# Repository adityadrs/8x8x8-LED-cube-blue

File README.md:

8x8x8 LED Cube Blue

Sources contain original files (design and code) that I used to build my cube around

Code added to impliment multiplexing, there are some issues with dynamic implimentation but when things are hard coded, multiplexing works fine ( Basic.ino )

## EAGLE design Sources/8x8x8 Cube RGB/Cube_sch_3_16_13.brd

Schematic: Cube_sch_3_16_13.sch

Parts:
C1, C6, C7, C16, C17, C18, C19, C20, C21, C22, C23, C24, C25, C26, C27, C28, C29, C30, C31, C32, C33, C34, C35, C36, C37, C38: 0.1uF; C2.5-3
C2: 10uF; C2.5-3
C3, C8, C9, C10, C11, C12, C13, C14, C15: 100uF; C2.5-3
C4, C5: 22pf; C2.5-3
C39: 0.1uf; C2.5-3
IC1, IC3, IC4, IC5, IC6, IC7, IC8, IC9, IC10, IC11, IC12, IC13, IC14, IC15, IC16, IC17, IC18, IC19, IC20, IC21, IC22, IC23, IC24, IC25, IC26: 74HC595N; DIL16
IC2: SMARTPRJ_ATMEGA328P-PU; SMARTPRJ_DIL28-3
Q1: 16MHz; HC49/S
Q2, Q3, Q4, Q5, Q6, Q7, Q8, Q9: IRF9Z34N; TO220BV
R1, R3, R5, R6, R8, R9, R11, R12, R14, R15, R17, R18, R20, R21, R23, R24, R26, R27, R30, R31, R34, R35, R38, R39, R42, R43, R46, R47, R50, R51, R54, R55, R58, R59, R62, R63, R66, R67, R70, R71, R74, R75, R78, R79, R82, R83, R86, R87, R90, R91, R94, R95, R98, R99, R102, R103, R106, R107, R110, R111, R114, R115, R118, R119, R122, R123, R126, R127, R130, R131, R134, R135, R138, R139, R142, R143, R146, R147, R150, R151, R154, R155, R158, R159, R162, R163, R166, R167, R170, R171, R174, R175, R178, R179, R182, R183, R186, R187, R190, R191, R194, R195, R198, R199, R202, R203, R206, R207, R210, R211, R214, R215, R218, R219, R222, R223, R226, R227, R230, R231, R234, R235, R238, R239, R242, R243, R246, R247, R250, R251, R254, R255, R258, R259, R262, R263, R266, R267, R270, R271, R274, R275, R278, R279, R282, R283, R286, R287, R290, R291, R294, R295, R298, R299, R302, R303, R306, R307, R310, R311, R314, R315, R318, R319, R322, R323, R326, R327, R330, R331, R334, R335, R338, R339, R342, R343, R346, R347, R350, R351, R354, R355, R358, R359, R362, R363, R366, R367, R370, R371, R374, R375, R378, R379, R382, R383, R386, R387, R390, R391, R394, R395, R398, R399, R402, R403, R406, R407, R410, R411, R414, R415, R418, R419, R422, R423, R426, R427, R430, R431, R434, R435, R438, R439, R442, R443, R446, R447, R450, R451, R454, R455, R458, R459, R462, R463, R466, R467, R470, R471, R474, R475, R478, R479, R482, R483, R486, R487, R490, R491, R494, R495, R498, R499, R502, R503, R506, R507, R510, R511, R514, R515, R518, R519, R522, R523, R526, R527, R530, R531, R534, R535, R538, R539, R541, R542, R543, R545, R546, R547, R550, R551, R553, R554, R555, R557, R558, R559, R562, R563, R565, R566, R567, R569, R571, R572, R574, R575, R577, R578, R580, R581, R583, R584, R586, R587, R589, R590, R592, R593, R595, R596, R598, R599, R601, R602, R604, R605, R607, R608, R610, R611, R613, R614, R616, R617, R619, R620, R622, R623, R625, R626, R628, R629, R631, R632, R634, R635, R637, R638, R640, R641, R643, R644, R646, R647, R649, R650, R652, R653, R655, R656, R658, R659, R661, R662, R664, R665, R667, R668, R670, R671, R673, R674, R676, R677, R679, R680, R682, R683, R685, R686, R688, R689, R691, R692, R694, R695, R697, R698, R700, R701, R703, R704, R706, R707, R709, R710, R712, R713, R715, R716, R718, R719, R721, R722, R724, R725, R727, R728: 1k; 0204/5
R2, R730: 10k; 0204/5
R4, R7, R10, R13, R16, R19, R22, R25, R28, R29, R32, R33, R36, R37, R40, R41, R44, R45, R48, R49, R52, R53, R56, R57, R60, R61, R64, R65, R68, R69, R72, R73, R76, R77, R80, R81, R84, R85, R88, R89, R92, R93, R96, R97, R100, R101, R104, R105, R108, R109, R112, R113, R116, R117, R120, R121, R124, R125, R128, R129, R132, R133, R136, R137, R140, R141, R144, R145, R148, R149, R152, R153, R156, R157, R160, R161, R164, R165, R168, R169, R172, R173, R176, R177, R180, R181, R184, R185, R188, R189, R192, R193, R196, R197, R200, R201, R204, R205, R208, R209, R212, R213, R216, R217, R220, R221, R224, R225, R228, R229, R232, R233, R236, R237, R240, R241, R244, R245, R248, R249, R252, R253, R256, R257, R260, R261, R264, R265, R268, R269, R272, R273, R276, R277, R280, R281, R284, R285, R288, R289, R292, R293, R296, R297, R300, R301, R304, R305, R308, R309, R312, R313, R316, R317, R320, R321, R324, R325, R328, R329, R332, R333, R336, R337, R340, R341, R344, R345, R348, R349, R352, R353, R356, R357, R360, R361, R364, R365, R368, R369, R372, R373, R376, R377, R380, R381, R384, R385, R388, R389, R392, R393, R396, R397, R400, R401, R404, R405, R408, R409, R412, R413, R416, R417, R420, R421, R424, R425, R428, R429, R432, R433, R436, R437, R440, R441, R444, R445, R448, R449, R452, R453, R456, R457, R460, R461, R464, R465, R468, R469, R472, R473, R476, R477, R480, R481, R484, R485, R488, R489, R492, R493, R496, R497, R500, R501, R504, R505, R508, R509, R512, R513, R516, R517, R520, R521, R524, R525, R528, R529, R532, R533, R536, R537, R540, R544, R548, R549, R552, R556, R560, R561, R564, R568, R570, R573, R576, R579, R582, R585, R588, R591, R594, R597, R600, R603, R606, R609, R612, R615, R618, R621, R624, R627, R630, R633, R636, R639, R642, R645, R648, R651, R654, R657, R660, R663, R666, R669, R672, R675, R678, R681, R684, R687, R690, R693, R696, R699, R702, R705, R708, R711, R714, R717, R720, R723, R726, R729: 100; 0204/5
SV1: MA04-1
SV2: MA05-1
T1, T2, T3, T4, T5, T6, T7, T8, T9, T10, T11, T12, T13, T14, T15, T16, T17, T18, T19, T20, T21, T22, T23, T24, T25, T26, T27, T28, T29, T30, T31, T32, T33, T34, T35, T36, T37, T38, T39, T40, T41, T42, T43, T44, T45, T46, T47, T48, T49, T50, T51, T52, T53, T54, T55, T56, T57, T58, T59, T60, T61, T62, T63, T64, T65, T66, T67, T68, T69, T70, T71, T72, T73, T74, T75, T76, T77, T78, T79, T80, T81, T82, T83, T84, T85, T86, T87, T88, T89, T90, T91, T92, T93, T94, T95, T96, T97, T98, T99, T100, T101, T102, T103, T104, T105, T106, T107, T108, T109, T110, T111, T112, T113, T114, T115, T116, T117, T118, T119, T120, T121, T122, T123, T124, T125, T126, T127, T128, T129, T130, T131, T132, T133, T134, T135, T136, T137, T138, T139, T140, T141, T142, T143, T144, T145, T146, T147, T148, T149, T150, T151, T152, T153, T154, T155, T156, T157, T158, T159, T160, T161, T162, T163, T164, T165, T166, T167, T168, T169, T170, T171, T172, T173, T174, T175, T176, T177, T178, T179, T180, T181, T182, T183, T184, T185, T186, T187, T188, T189, T190, T191, T192, T193, T194, T195, T196, T197, T198, T199, T200: 2N3904; TO92

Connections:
+5V: C1.1, C2.1, C3.1, C6.1, C7.1, C8.1, C9.1, C10.1, C11.1, C12.1, C13.1, C14.1, C15.1, C16.1, C17.1, C18.1, C19.1, C20.1, C21.1, C22.1, C23.1, C24.1, C25.1, C26.1, C27.1, C28.1, C29.1, C30.1, C31.1, C32.1, C33.1, C34.1, C35.1, C36.1, C37.1, C38.1, IC1.10 (SCL), IC1.16 (VCC), IC2.7 (VCC), IC2.20 (AVCC), IC2.21 (AREF), IC3.10 (SCL), IC3.16 (VCC), IC4.10 (SCL), IC4.16 (VCC), IC5.10 (SCL), IC5.16 (VCC), IC6.10 (SCL), IC6.16 (VCC), IC7.10 (SCL), IC7.16 (VCC), IC8.10 (SCL), IC8.16 (VCC), IC9.10 (SCL), IC9.16 (VCC), IC10.10 (SCL), IC10.16 (VCC), IC11.10 (SCL), IC11.16 (VCC), IC12.10 (SCL), IC12.16 (VCC), IC13.10 (SCL), IC13.16 (VCC), IC14.10 (SCL), IC14.16 (VCC), IC15.10 (SCL), IC15.16 (VCC), IC16.10 (SCL), IC16.16 (VCC), IC17.10 (SCL), IC17.16 (VCC), IC18.10 (SCL), IC18.16 (VCC), IC19.10 (SCL), IC19.16 (VCC), IC20.10 (SCL), IC20.16 (VCC), IC21.10 (SCL), IC21.16 (VCC), IC22.10 (SCL), IC22.16 (VCC), IC23.10 (SCL), IC23.16 (VCC), IC24.10 (SCL), IC24.16 (VCC), IC25.10 (SCL), IC25.16 (VCC), IC26.10 (SCL), IC26.16 (VCC), Q2.S, Q3.S, Q4.S, Q5.S, Q6.S, Q7.S, Q8.S, Q9.S, R2.2, R3.2, R6.2, R9.2, R12.2, R15.2, R18.2, R21.2, R24.2, R27.2, R31.2, R35.2, R39.2, R43.2, R47.2, R51.2, R55.2, R59.2, R63.2, R67.2, R71.2, R75.2, R79.2, R83.2, R87.2, R91.2, R95.2, R99.2, R103.2, R107.2, R111.2, R115.2, R119.2, R123.2, R127.2, R131.2, R135.2, R139.2, R143.2, R147.2, R151.2, R155.2, R159.2, R163.2, R167.2, R171.2, R175.2, R179.2, R183.2, R187.2, R191.2, R195.2, R199.2, R203.2, R207.2, R211.2, R215.2, R219.2, R223.2, R227.2, R231.2, R235.2, R239.2, R243.2, R247.2, R251.2, R255.2, R259.2, R263.2, R267.2, R271.2, R275.2, R279.2, R283.2, R287.2, R291.2, R295.2, R299.2, R303.2, R307.2, R311.2, R315.2, R319.2, R323.2, R327.2, R331.2, R335.2, R339.2, R343.2, R347.2, R351.2, R355.2, R359.2, R363.2, R367.2, R371.2, R375.2, R379.2, R383.2, R387.2, R391.2, R395.2, R399.2, R403.2, R407.2, R411.2, R415.2, R419.2, R423.2, R427.2, R431.2, R435.2, R439.2, R443.2, R447.2, R451.2, R455.2, R459.2, R463.2, R467.2, R471.2, R475.2, R479.2, R483.2, R487.2, R491.2, R495.2, R499.2, R503.2, R507.2, R511.2, R515.2, R519.2, R523.2, R527.2, R531.2, R535.2, R539.2, R543.2, R545.2, R547.2, R551.2, R555.2, R557.2, R559.2, R563.2, R567.2, R569.2, R572.2, R575.2, R578.2, R581.2, R584.2, R587.2, R590.2, R593.2, R596.2, R599.2, R602.2, R605.2, R608.2, R611.2, R614.2, R617.2, R620.2, R623.2, R626.2, R629.2, R632.2, R635.2, R638.2, R641.2, R644.2, R647.2, R650.2, R653.2, R656.2, R659.2, R662.2, R665.2, R668.2, R671.2, R674.2, R677.2, R680.2, R683.2, R686.2, R689.2, R692.2, R695.2, R698.2, R701.2, R704.2, R707.2, R710.2, R713.2, R716.2, R719.2, R722.2, R725.2, R728.2, SV1.2
ANODE_LEVEL_0: Q2.D, R4.2
ANODE_LEVEL_1: Q3.D, R7.2
ANODE_LEVEL_2: Q4.D, R10.2
ANODE_LEVEL_3: Q5.D, R13.2
ANODE_LEVEL_4: Q6.D, R16.2
ANODE_LEVEL_5: Q7.D, R19.2
ANODE_LEVEL_6: Q8.D, R22.2
ANODE_LEVEL_7: Q9.D, R25.2
BLANK: IC1.13 (G), IC2.6 ((T0)PD4), IC3.13 (G), IC4.13 (G), IC5.13 (G), IC6.13 (G), IC7.13 (G), IC8.13 (G), IC9.13 (G), IC10.13 (G), IC11.13 (G), IC12.13 (G), IC13.13 (G), IC14.13 (G), IC15.13 (G), IC16.13 (G), IC17.13 (G), IC18.13 (G), IC19.13 (G), IC20.13 (G), IC21.13 (G), IC22.13 (G), IC23.13 (G), IC24.13 (G), IC25.13 (G), IC26.13 (G), R2.1
BL_IN_0: IC1.15 (QA), R26.1
BL_IN_1: IC1.1 (QB), R30.1
BL_IN_2: IC1.2 (QC), R34.1
BL_IN_3: IC1.3 (QD), R38.1
BL_IN_4: IC1.4 (QE), R42.1
BL_IN_5: IC1.5 (QF), R46.1
BL_IN_6: IC1.6 (QG), R50.1
BL_IN_7: IC1.7 (QH), R54.1
BL_IN_8: IC4.15 (QA), R58.1
BL_IN_9: IC4.1 (QB), R62.1
BL_IN_10: IC4.2 (QC), R66.1
BL_IN_11: IC4.3 (QD), R70.1
BL_IN_12: IC4.4 (QE), R74.1
BL_IN_13: IC4.5 (QF), R78.1
BL_IN_14: IC4.6 (QG), R82.1
BL_IN_15: IC4.7 (QH), R86.1
BL_IN_16: IC5.15 (QA), R90.1
BL_IN_17: IC5.1 (QB), R94.1
BL_IN_18: IC5.2 (QC), R98.1
BL_IN_19: IC5.3 (QD), R102.1
BL_IN_20: IC5.4 (QE), R106.1
BL_IN_21: IC5.5 (QF), R110.1
BL_IN_22: IC5.6 (QG), R114.1
BL_IN_23: IC5.7 (QH), R118.1
BL_IN_24: IC6.15 (QA), R122.1
BL_IN_25: IC6.1 (QB), R126.1
BL_IN_26: IC6.2 (QC), R130.1
BL_IN_27: IC6.3 (QD), R134.1
BL_IN_28: IC6.4 (QE), R138.1
BL_IN_29: IC6.5 (QF), R142.1
BL_IN_30: IC6.6 (QG), R146.1
BL_IN_31: IC6.7 (QH), R150.1
BL_IN_32: IC7.15 (QA), R154.1
BL_IN_33: IC7.1 (QB), R158.1
BL_IN_34: IC7.2 (QC), R162.1
BL_IN_35: IC7.3 (QD), R166.1
BL_IN_36: IC7.4 (QE), R170.1
BL_IN_37: IC7.5 (QF), R174.1
BL_IN_38: IC7.6 (QG), R178.1
BL_IN_39: IC7.7 (QH), R182.1
BL_IN_40: IC8.15 (QA), R186.1
BL_IN_41: IC8.1 (QB), R190.1
BL_IN_42: IC8.2 (QC), R194.1
BL_IN_43: IC8.3 (QD), R198.1
BL_IN_44: IC8.4 (QE), R202.1
BL_IN_45: IC8.5 (QF), R206.1
BL_IN_46: IC8.6 (QG), R210.1
BL_IN_47: IC8.7 (QH), R214.1
BL_IN_48: IC9.15 (QA), R218.1
BL_IN_49: IC9.1 (QB), R222.1
BL_IN_50: IC9.2 (QC), R226.1
BL_IN_51: IC9.3 (QD), R230.1
BL_IN_52: IC9.4 (QE), R234.1
BL_IN_53: IC9.5 (QF), R238.1
BL_IN_54: IC9.6 (QG), R242.1
BL_IN_55: IC9.7 (QH), R246.1
BL_IN_56: IC10.15 (QA), R250.1
BL_IN_57: IC10.1 (QB), R254.1
BL_IN_58: IC10.2 (QC), R258.1
BL_IN_59: IC10.3 (QD), R262.1
BL_IN_60: IC10.4 (QE), R266.1
BL_IN_61: IC10.5 (QF), R270.1
BL_IN_62: IC10.6 (QG), R274.1
BL_IN_63: IC10.7 (QH), R278.1
BL_OU_0: R28.2, R29.2
BL_OU_1: R32.2, R33.2
BL_OU_2: R36.2, R37.2
BL_OU_3: R40.2, R41.2
BL_OU_4: R44.2, R45.2
BL_OU_5: R48.2, R49.2
BL_OU_6: R52.2, R53.2
BL_OU_7: R56.2, R57.2
BL_OU_8: R60.2, R61.2
BL_OU_9: R64.2, R65.2
BL_OU_10: R68.2, R69.2
BL_OU_11: R72.2, R73.2
BL_OU_12: R76.2, R77.2
BL_OU_13: R80.2, R81.2
BL_OU_14: R84.2, R85.2
BL_OU_15: R88.2, R89.2
BL_OU_16: R92.2, R93.2
BL_OU_17: R96.2, R97.2
BL_OU_18: R100.2, R101.2
BL_OU_19: R104.2, R105.2
BL_OU_20: R108.2, R109.2
BL_OU_21: R112.2, R113.2
BL_OU_22: R116.2, R117.2
BL_OU_23: R120.2, R121.2
BL_OU_24: R124.2, R125.2
BL_OU_25: R128.2, R129.2
BL_OU_26: R132.2, R133.2
BL_OU_27: R136.2, R137.2
BL_OU_28: R140.2, R141.2
BL_OU_29: R144.2, R145.2
BL_OU_30: R148.2, R149.2
BL_OU_32: R152.2, R153.2, R156.2, R157.2
BL_OU_33: R160.2, R161.2
BL_OU_34: R164.2, R165.2
BL_OU_35: R168.2, R169.2
BL_OU_36: R172.2, R173.2
BL_OU_37: R176.2, R177.2
BL_OU_38: R180.2, R181.2
BL_OU_39: R184.2, R185.2
BL_OU_40: R188.2, R189.2
BL_OU_41: R192.2, R193.2
BL_OU_42: R196.2, R197.2
BL_OU_43: R200.2, R201.2
BL_OU_44: R204.2, R205.2
BL_OU_45: R208.2, R209.2
BL_OU_46: R212.2, R213.2
BL_OU_47: R216.2, R217.2
BL_OU_48: R220.2, R221.2
BL_OU_49: R224.2, R225.2
BL_OU_50: R228.2, R229.2
BL_OU_51: R232.2, R233.2
BL_OU_52: R236.2, R237.2
BL_OU_53: R240.2, R241.2
BL_OU_54: R244.2, R245.2
BL_OU_55: R248.2, R249.2
BL_OU_56: R252.2, R253.2
BL_OU_57: R256.2, R257.2
BL_OU_58: R260.2, R261.2
BL_OU_59: R264.2, R265.2
BL_OU_60: R268.2, R269.2
BL_OU_61: R272.2, R273.2
BL_OU_62: R276.2, R277.2
BL_OU_63: R280.2, R281.2
CLOCK: IC1.11 (SCK), IC2.19 ((SCK)PB5), IC3.11 (SCK), IC4.11 (SCK), IC5.11 (SCK), IC6.11 (SCK), IC7.11 (SCK), IC8.11 (SCK), IC9.11 (SCK), IC10.11 (SCK), IC11.11 (SCK), IC12.11 (SCK), IC13.11 (SCK), IC14.11 (SCK), IC15.11 (SCK), IC16.11 (SCK), IC17.11 (SCK), IC18.11 (SCK), IC19.11 (SCK), IC20.11 (SCK), IC21.11 (SCK), IC22.11 (SCK), IC23.11 (SCK), IC24.11 (SCK), IC25.11 (SCK), IC26.11 (SCK)
CNTRL_L0: IC3.7 (QH), R1.1
CNTRL_L1: IC3.6 (QG), R5.1
CNTRL_L2: IC3.5 (QF), R8.1
CNTRL_L3: IC3.4 (QE), R11.1
CNTRL_L4: IC3.3 (QD), R14.1
CNTRL_L5: IC3.2 (QC), R17.1
CNTRL_L6: IC3.1 (QB), R20.1
CNTRL_L7: IC3.15 (QA), R23.1
DATA: IC2.17 ((MOSI)PB3), IC3.14 (SER)
DTR_RESET: C39.2, IC2.1 (RESET), R730.1
GND: C1.2, C2.2, C3.2, C4.1, C5.1, C6.2, C7.2, C8.2, C9.2, C10.2, C11.2, C12.2, C13.2, C14.2, C15.2, C16.2, C17.2, C18.2, C19.2, C20.2, C21.2, C22.2, C23.2, C24.2, C25.2, C26.2, C27.2, C28.2, C29.2, C30.2, C31.2, C32.2, C33.2, C34.2, C35.2, C36.2, C37.2, C38.2, IC1.8 (GND), IC2.8 (GND), IC2.22 (AGND), IC3.8 (GND), IC4.8 (GND), IC5.8 (GND), IC6.8 (GND), IC7.8 (GND), IC8.8 (GND), IC9.8 (GND), IC10.8 (GND), IC11.8 (GND), IC12.8 (GND), IC13.8 (GND), IC14.8 (GND), IC15.8 (GND), IC16.8 (GND), IC17.8 (GND), IC18.8 (GND), IC19.8 (GND), IC20.8 (GND), IC21.8 (GND), IC22.8 (GND), IC23.8 (GND), IC24.8 (GND), IC25.8 (GND), IC26.8 (GND), R4.1, R7.1, R10.1, R13.1, R16.1, R19.1, R22.1, R25.1, SV1.1, T1.3 (E), T2.3 (E), T3.3 (E), T4.3 (E), T5.3 (E), T6.3 (E), T7.3 (E), T8.3 (E), T9.3 (E), T10.3 (E), T11.3 (E), T12.3 (E), T13.3 (E), T14.3 (E), T15.3 (E), T16.3 (E), T17.3 (E), T18.3 (E), T19.3 (E), T20.3 (E), T21.3 (E), T22.3 (E), T23.3 (E), T24.3 (E), T25.3 (E), T26.3 (E), T27.3 (E), T28.3 (E), T29.3 (E), T30.3 (E), T31.3 (E), T32.3 (E), T33.3 (E), T34.3 (E), T35.3 (E), T36.3 (E), T37.3 (E), T38.3 (E), T39.3 (E), T40.3 (E), T41.3 (E), T42.3 (E), T43.3 (E), T44.3 (E), T45.3 (E), T46.3 (E), T47.3 (E), T48.3 (E), T49.3 (E), T50.3 (E), T51.3 (E), T52.3 (E), T53.3 (E), T54.3 (E), T55.3 (E), T56.3 (E), T57.3 (E), T58.3 (E), T59.3 (E), T60.3 (E), T61.3 (E), T62.3 (E), T63.3 (E), T64.3 (E), T65.3 (E), T66.3 (E), T67.3 (E), T68.3 (E), T69.3 (E), T70.3 (E), T71.3 (E), T72.3 (E), T73.3 (E), T74.3 (E), T75.3 (E), T76.3 (E), T77.3 (E), T78.3 (E), T79.3 (E), T80.3 (E), T81.3 (E), T82.3 (E), T83.3 (E), T84.3 (E), T85.3 (E), T86.3 (E), T87.3 (E), T88.3 (E), T89.3 (E), T90.3 (E), T91.3 (E), T92.3 (E), T93.3 (E), T94.3 (E), T95.3 (E), T96.3 (E), T97.3 (E), T98.3 (E), T99.3 (E), T100.3 (E), T101.3 (E), T102.3 (E), T103.3 (E), T104.3 (E), T105.3 (E), T106.3 (E), T107.3 (E), T108.3 (E), T109.3 (E), T110.3 (E), T111.3 (E), T112.3 (E), T113.3 (E), T114.3 (E), T115.3 (E), T116.3 (E), T117.3 (E), T118.3 (E), T119.3 (E), T120.3 (E), T121.3 (E), T122.3 (E), T123.3 (E), T124.3 (E), T125.3 (E), T126.3 (E), T127.3 (E), T128.3 (E), T129.3 (E), T130.3 (E), T131.3 (E), T132.3 (E), T133.3 (E), T134.3 (E), T135.3 (E), T136.3 (E), T137.3 (E), T138.3 (E), T139.3 (E), T140.3 (E), T141.3 (E), T142.3 (E), T143.3 (E), T144.3 (E), T145.3 (E), T146.3 (E), T147.3 (E), T148.3 (E), T149.3 (E), T150.3 (E), T151.3 (E), T152.3 (E), T153.3 (E), T154.3 (E), T155.3 (E), T156.3 (E), T157.3 (E), T158.3 (E), T159.3 (E), T160.3 (E), T161.3 (E), T162.3 (E), T163.3 (E), T164.3 (E), T165.3 (E), T166.3 (E), T167.3 (E), T168.3 (E), T169.3 (E), T170.3 (E), T171.3 (E), T172.3 (E), T173.3 (E), T174.3 (E), T175.3 (E), T176.3 (E), T177.3 (E), T178.3 (E), T179.3 (E), T180.3 (E), T181.3 (E), T182.3 (E), T183.3 (E), T184.3 (E), T185.3 (E), T186.3 (E), T187.3 (E), T188.3 (E), T189.3 (E), T190.3 (E), T191.3 (E), T192.3 (E), T193.3 (E), T194.3 (E), T195.3 (E), T196.3 (E), T197.3 (E), T198.3 (E), T199.3 (E), T200.3 (E)
GR_IN_0: IC12.15 (QA), R314.1
GR_IN_1: IC12.1 (QB), R318.1
GR_IN_2: IC12.2 (QC), R322.1
GR_IN_3: IC12.3 (QD), R326.1
GR_IN_4: IC12.4 (QE), R330.1
GR_IN_5: IC12.5 (QF), R334.1
GR_IN_6: IC12.6 (QG), R338.1
GR_IN_7: IC12.7 (QH), R342.1
GR_IN_8: IC13.15 (QA), R346.1
GR_IN_9: IC13.1 (QB), R350.1
GR_IN_10: IC13.2 (QC), R354.1
GR_IN_11: IC13.3 (QD), R358.1
GR_IN_12: IC13.4 (QE), R362.1
GR_IN_13: IC13.5 (QF), R366.1
GR_IN_14: IC13.6 (QG), R370.1
GR_IN_15: IC13.7 (QH), R374.1
GR_IN_16: IC14.15 (QA), R378.1
GR_IN_17: IC14.1 (QB), R382.1
GR_IN_18: IC14.2 (QC), R386.1
GR_IN_19: IC14.3 (QD), R390.1
GR_IN_20: IC14.4 (QE), R394.1
GR_IN_21: IC14.5 (QF), R398.1
GR_IN_22: IC14.6 (QG), R402.1
GR_IN_23: IC14.7 (QH), R406.1
GR_IN_24: IC15.15 (QA), R410.1
GR_IN_25: IC15.1 (QB), R414.1
GR_IN_26: IC15.2 (QC), R418.1
GR_IN_27: IC15.3 (QD), R422.1
GR_IN_28: IC15.4 (QE), R426.1
GR_IN_29: IC15.5 (QF), R430.1
GR_IN_30: IC15.6 (QG), R434.1
GR_IN_31: IC15.7 (QH), R438.1
GR_IN_32: IC16.15 (QA), R442.1
GR_IN_33: IC16.1 (QB), R446.1
GR_IN_34: IC16.2 (QC), R450.1
GR_IN_35: IC16.3 (QD), R454.1
GR_IN_36: IC16.4 (QE), R458.1
GR_IN_37: IC16.5 (QF), R462.1
GR_IN_38: IC16.6 (QG), R466.1
GR_IN_39: IC16.7 (QH), R470.1
GR_IN_40: IC17.15 (QA), R474.1
GR_IN_41: IC17.1 (QB), R478.1
GR_IN_42: IC17.2 (QC), R482.1
GR_IN_43: IC17.3 (QD), R486.1
GR_IN_44: IC17.4 (QE), R490.1
GR_IN_45: IC17.5 (QF), R494.1
GR_IN_46: IC17.6 (QG), R498.1
GR_IN_47: IC17.7 (QH), R502.1
GR_IN_48: IC18.15 (QA), R506.1
GR_IN_49: IC18.1 (QB), R510.1
GR_IN_50: IC18.2 (QC), R514.1
GR_IN_51: IC18.3 (QD), R518.1
GR_IN_52: IC18.4 (QE), R522.1
GR_IN_53: IC18.5 (QF), R526.1
GR_IN_54: IC18.6 (QG), R530.1
GR_IN_55: IC18.7 (QH), R534.1
GR_IN_56: IC19.15 (QA), R282.1
GR_IN_57: IC19.1 (QB), R286.1
GR_IN_58: IC19.2 (QC), R290.1
GR_IN_59: IC19.3 (QD), R294.1
GR_IN_60: IC19.4 (QE), R298.1
GR_IN_61: IC19.5 (QF), R302.1
GR_IN_62: IC19.6 (QG), R306.1
GR_IN_63: IC19.7 (QH), R310.1
GR_OU_0: R316.2, R317.2
GR_OU_1: R320.2, R321.2
GR_OU_2: R324.2, R325.2
GR_OU_3: R328.2, R329.2
GR_OU_4: R332.2, R333.2
GR_OU_5: R336.2, R337.2
GR_OU_6: R340.2, R341.2
GR_OU_7: R344.2, R345.2
GR_OU_8: R348.2, R349.2
GR_OU_9: R352.2, R353.2
GR_OU_10: R356.2, R357.2
GR_OU_11: R360.2, R361.2
GR_OU_12: R364.2, R365.2
GR_OU_13: R368.2, R369.2
GR_OU_14: R372.2, R373.2
GR_OU_15: R376.2, R377.2
GR_OU_16: R380.2, R381.2
GR_OU_17: R384.2, R385.2
GR_OU_18: R388.2, R389.2
GR_OU_19: R392.2, R393.2
GR_OU_20: R396.2, R397.2
GR_OU_21: R400.2, R401.2
GR_OU_22: R404.2, R405.2
GR_OU_23: R408.2, R409.2
GR_OU_24: R412.2, R413.2
GR_OU_25: R416.2, R417.2
GR_OU_26: R420.2, R421.2
GR_OU_27: R424.2, R425.2
GR_OU_28: R428.2, R429.2
GR_OU_29: R432.2, R433.2
GR_OU_30: R436.2, R437.2
GR_OU_31: R440.2, R441.2
GR_OU_32: R444.2, R445.2
GR_OU_33: R448.2, R449.2
GR_OU_34: R452.2, R453.2
GR_OU_35: R456.2, R457.2
GR_OU_36: R460.2, R461.2
GR_OU_37: R464.2, R465.2
GR_OU_38: R468.2, R469.2
GR_OU_39: R472.2, R473.2
GR_OU_40: R476.2, R477.2
GR_OU_41: R480.2, R481.2
GR_OU_42: R484.2, R485.2
GR_OU_43: R488.2, R489.2
GR_OU_44: R492.2, R493.2
GR_OU_45: R496.2, R497.2
GR_OU_46: R500.2, R501.2
GR_OU_47: R504.2, R505.2
GR_OU_48: R508.2, R509.2
GR_OU_49: R512.2, R513.2
GR_OU_50: R516.2, R517.2
GR_OU_51: R520.2, R521.2
GR_OU_52: R524.2, R525.2
GR_OU_53: R528.2, R529.2
GR_OU_54: R532.2, R533.2
GR_OU_55: R536.2, R537.2
GR_OU_56: R284.2, R285.2
GR_OU_57: R288.2, R289.2
GR_OU_58: R292.2, R293.2
GR_OU_59: R296.2, R297.2
GR_OU_60: R300.2, R301.2
GR_OU_61: R304.2, R305.2
GR_OU_62: R308.2, R309.2
GR_OU_63: R312.2, R313.2
LATCH: IC1.12 (RCK), IC2.4 ((INT0)PD2), IC3.12 (RCK), IC4.12 (RCK), IC5.12 (RCK), IC6.12 (RCK), IC7.12 (RCK), IC8.12 (RCK), IC9.12 (RCK), IC10.12 (RCK), IC11.12 (RCK), IC12.12 (RCK), IC13.12 (RCK), IC14.12 (RCK), IC15.12 (RCK), IC16.12 (RCK), IC17.12 (RCK), IC18.12 (RCK), IC19.12 (RCK), IC20.12 (RCK), IC21.12 (RCK), IC22.12 (RCK), IC23.12 (RCK), IC24.12 (RCK), IC25.12 (RCK), IC26.12 (RCK)
unnamed: IC1.14 (SER), IC3.9 (QH*)
unnamed: C4.2, IC2.9 (XTAL1), Q1.2
unnamed: R1.2, T1.2 (B)
unnamed: C5.2, IC2.10 (XTAL2), Q1.1
unnamed: Q2.G, R3.1, T1.1 (C)
unnamed: R5.2, T2.2 (B)
unnamed: Q3.G, R6.1, T2.1 (C)
unnamed: R8.2, T3.2 (B)
unnamed: Q4.G, R9.1, T3.1 (C)
unnamed: R11.2, T4.2 (B)
unnamed: Q5.G, R12.1, T4.1 (C)
unnamed: R14.2, T5.2 (B)
unnamed: Q6.G, R15.1, T5.1 (C)
unnamed: R17.2, T6.2 (B)
unnamed: Q7.G, R18.1, T6.1 (C)
unnamed: R20.2, T7.2 (B)
unnamed: Q8.G, R21.1, T7.1 (C)
unnamed: R23.2, T8.2 (B)
unnamed: Q9.G, R24.1, T8.1 (C)
unnamed: R26.2, T9.2 (B)
unnamed: R27.1, R28.1, R29.1, T9.1 (C)
unnamed: R30.2, T10.2 (B)
unnamed: R31.1, R32.1, R33.1, T10.1 (C)
unnamed: R34.2, T11.2 (B)
unnamed: R35.1, R36.1, R37.1, T11.1 (C)
unnamed: R38.2, T12.2 (B)
unnamed: R39.1, R40.1, R41.1, T12.1 (C)
unnamed: R42.2, T13.2 (B)
unnamed: R43.1, R44.1, R45.1, T13.1 (C)
unnamed: R46.2, T14.2 (B)
unnamed: R47.1, R48.1, R49.1, T14.1 (C)
unnamed: R50.2, T15.2 (B)
unnamed: R51.1, R52.1, R53.1, T15.1 (C)
unnamed: R54.2, T16.2 (B)
unnamed: R55.1, R56.1, R57.1, T16.1 (C)
unnamed: R58.2, T17.2 (B)
unnamed: R59.1, R60.1, R61.1, T17.1 (C)
unnamed: R62.2, T18.2 (B)
unnamed: R63.1, R64.1, R65.1, T18.1 (C)
unnamed: R66.2, T19.2 (B)
unnamed: R67.1, R68.1, R69.1, T19.1 (C)
unnamed: R70.2, T20.2 (B)
unnamed: R71.1, R72.1, R73.1, T20.1 (C)
unnamed: R74.2, T21.2 (B)
unnamed: R75.1, R76.1, R77.1, T21.1 (C)
unnamed: R78.2, T22.2 (B)
unnamed: R79.1, R80.1, R81.1, T22.1 (C)
unnamed: R82.2, T23.2 (B)
unnamed: R83.1, R84.1, R85.1, T23.1 (C)
unnamed: R86.2, T24.2 (B)
unnamed: R87.1, R88.1, R89.1, T24.1 (C)
unnamed: R90.2, T25.2 (B)
unnamed: R91.1, R92.1, R93.1, T25.1 (C)
unnamed: R94.2, T26.2 (B)
unnamed: R95.1, R96.1, R97.1, T26.1 (C)
unnamed: R98.2, T27.2 (B)
unnamed: R99.1, R100.1, R101.1, T27.1 (C)
unnamed: R102.2, T28.2 (B)
unnamed: R103.1, R104.1, R105.1, T28.1 (C)
unnamed: R106.2, T29.2 (B)
unnamed: R107.1, R108.1, R109.1, T29.1 (C)
unnamed: R110.2, T30.2 (B)
unnamed: R111.1, R112.1, R113.1, T30.1 (C)
unnamed: R114.2, T31.2 (B)
unnamed: R115.1, R116.1, R117.1, T31.1 (C)
unnamed: R118.2, T32.2 (B)
unnamed: R119.1, R120.1, R121.1, T32.1 (C)
unnamed: R122.2, T33.2 (B)
unnamed: R123.1, R124.1, R125.1, T33.1 (C)
unnamed: R126.2, T34.2 (B)
unnamed: R127.1, R128.1, R129.1, T34.1 (C)
unnamed: R130.2, T35.2 (B)
unnamed: R131.1, R132.1, R133.1, T35.1 (C)
unnamed: R134.2, T36.2 (B)
unnamed: R135.1, R136.1, R137.1, T36.1 (C)
unnamed: R138.2, T37.2 (B)
unnamed: R139.1, R140.1, R141.1, T37.1 (C)
unnamed: R142.2, T38.2 (B)
unnamed: R143.1, R144.1, R145.1, T38.1 (C)
unnamed: R146.2, T39.2 (B)
unnamed: R147.1, R148.1, R149.1, T39.1 (C)
unnamed: R150.2, T40.2 (B)
unnamed: R151.1, R152.1, R153.1, T40.1 (C)
unnamed: R154.2, T41.2 (B)
unnamed: R155.1, R156.1, R157.1, T41.1 (C)
unnamed: R158.2, T42.2 (B)
unnamed: R159.1, R160.1, R161.1, T42.1 (C)
unnamed: R162.2, T43.2 (B)
unnamed: R163.1, R164.1, R165.1, T43.1 (C)
unnamed: R166.2, T44.2 (B)
unnamed: R167.1, R168.1, R169.1, T44.1 (C)
unnamed: R170.2, T45.2 (B)
unnamed: R171.1, R172.1, R173.1, T45.1 (C)
unnamed: R174.2, T46.2 (B)
unnamed: R175.1, R176.1, R177.1, T46.1 (C)
unnamed: R178.2, T47.2 (B)
unnamed: R179.1, R180.1, R181.1, T47.1 (C)
unnamed: R182.2, T48.2 (B)
unnamed: R183.1, R184.1, R185.1, T48.1 (C)
unnamed: R186.2, T49.2 (B)
unnamed: R187.1, R188.1, R189.1, T49.1 (C)
unnamed: R190.2, T50.2 (B)
unnamed: R191.1, R192.1, R193.1, T50.1 (C)
unnamed: R194.2, T51.2 (B)
unnamed: R195.1, R196.1, R197.1, T51.1 (C)
unnamed: R198.2, T52.2 (B)
unnamed: R199.1, R200.1, R201.1, T52.1 (C)
unnamed: R202.2, T53.2 (B)
unnamed: R203.1, R204.1, R205.1, T53.1 (C)
unnamed: R206.2, T54.2 (B)
unnamed: R207.1, R208.1, R209.1, T54.1 (C)
unnamed: R210.2, T55.2 (B)
unnamed: R211.1, R212.1, R213.1, T55.1 (C)
unnamed: R214.2, T56.2 (B)
unnamed: R215.1, R216.1, R217.1, T56.1 (C)
unnamed: R218.2, T57.2 (B)
unnamed: R219.1, R220.1, R221.1, T57.1 (C)
unnamed: R222.2, T58.2 (B)
unnamed: R223.1, R224.1, R225.1, T58.1 (C)
unnamed: R226.2, T59.2 (B)
unnamed: R227.1, R228.1, R229.1, T59.1 (C)
unnamed: R230.2, T60.2 (B)
unnamed: R231.1, R232.1, R233.1, T60.1 (C)
unnamed: R234.2, T61.2 (B)
unnamed: R235.1, R236.1, R237.1, T61.1 (C)
unnamed: R238.2, T62.2 (B)
unnamed: R239.1, R240.1, R241.1, T62.1 (C)
unnamed: R242.2, T63.2 (B)
unnamed: R243.1, R244.1, R245.1, T63.1 (C)
unnamed: R246.2, T64.2 (B)
unnamed: R247.1, R248.1, R249.1, T64.1 (C)
unnamed: R250.2, T65.2 (B)
unnamed: R251.1, R252.1, R253.1, T65.1 (C)
unnamed: R254.2, T66.2 (B)
unnamed: R255.1, R256.1, R257.1, T66.1 (C)
unnamed: R258.2, T67.2 (B)
unnamed: R259.1, R260.1, R261.1, T67.1 (C)
unnamed: R262.2, T68.2 (B)
unnamed: R263.1, R264.1, R265.1, T68.1 (C)
unnamed: R266.2, T69.2 (B)
unnamed: R267.1, R268.1, R269.1, T69.1 (C)
unnamed: R270.2, T70.2 (B)
unnamed: R271.1, R272.1, R273.1, T70.1 (C)
unnamed: R274.2, T71.2 (B)
unnamed: R275.1, R276.1, R277.1, T71.1 (C)
unnamed: R278.2, T72.2 (B)
unnamed: R279.1, R280.1, R281.1, T72.1 (C)
unnamed: R282.2, T73.2 (B)
unnamed: R283.1, R284.1, R285.1, T73.1 (C)
unnamed: R286.2, T74.2 (B)
unnamed: R287.1, R288.1, R289.1, T74.1 (C)
unnamed: R290.2, T75.2 (B)
unnamed: R291.1, R292.1, R293.1, T75.1 (C)
unnamed: R294.2, T76.2 (B)
unnamed: R295.1, R296.1, R297.1, T76.1 (C)
unnamed: R298.2, T77.2 (B)
unnamed: R299.1, R300.1, R301.1, T77.1 (C)
unnamed: R302.2, T78.2 (B)
unnamed: R303.1, R304.1, R305.1, T78.1 (C)
unnamed: R306.2, T79.2 (B)
unnamed: R307.1, R308.1, R309.1, T79.1 (C)
unnamed: R310.2, T80.2 (B)
unnamed: R311.1, R312.1, R313.1, T80.1 (C)
unnamed: IC10.9 (QH*), IC12.14 (SER)
unnamed: R314.2, T81.2 (B)
unnamed: R315.1, R316.1, R317.1, T81.1 (C)
unnamed: R318.2, T82.2 (B)
unnamed: R319.1, R320.1, R321.1, T82.1 (C)
unnamed: R322.2, T83.2 (B)
unnamed: R323.1, R324.1, R325.1, T83.1 (C)
unnamed: R326.2, T84.2 (B)
unnamed: R327.1, R328.1, R329.1, T84.1 (C)
unnamed: R330.2, T85.2 (B)
unnamed: R331.1, R332.1, R333.1, T85.1 (C)
unnamed: R334.2, T86.2 (B)
unnamed: R335.1, R336.1, R337.1, T86.1 (C)
unnamed: R338.2, T87.2 (B)
unnamed: R339.1, R340.1, R341.1, T87.1 (C)
unnamed: R342.2, T88.2 (B)
unnamed: R343.1, R344.1, R345.1, T88.1 (C)
unnamed: IC12.9 (QH*), IC13.14 (SER)
unnamed: R346.2, T89.2 (B)
unnamed: R347.1, R348.1, R349.1, T89.1 (C)
unnamed: R350.2, T90.2 (B)
unnamed: R351.1, R352.1, R353.1, T90.1 (C)
unnamed: R354.2, T91.2 (B)
unnamed: R355.1, R356.1, R357.1, T91.1 (C)
unnamed: R358.2, T92.2 (B)
unnamed: R359.1, R360.1, R361.1, T92.1 (C)
unnamed: R362.2, T93.2 (B)
unnamed: R363.1, R364.1, R365.1, T93.1 (C)
unnamed: R366.2, T94.2 (B)
unnamed: R367.1, R368.1, R369.1, T94.1 (C)
unnamed: R370.2, T95.2 (B)
unnamed: R371.1, R372.1, R373.1, T95.1 (C)
unnamed: R374.2, T96.2 (B)
unnamed: R375.1, R376.1, R377.1, T96.1 (C)
unnamed: IC13.9 (QH*), IC14.14 (SER)
unnamed: R378.2, T97.2 (B)
unnamed: R379.1, R380.1, R381.1, T97.1 (C)
unnamed: R382.2, T98.2 (B)
unnamed: R383.1, R384.1, R385.1, T98.1 (C)
unnamed: R386.2, T99.2 (B)
unnamed: R387.1, R388.1, R389.1, T99.1 (C)
unnamed: R390.2, T100.2 (B)
unnamed: R391.1, R392.1, R393.1, T100.1 (C)
unnamed: R394.2, T101.2 (B)
unnamed: R395.1, R396.1, R397.1, T101.1 (C)
unnamed: R398.2, T102.2 (B)
unnamed: R399.1, R400.1, R401.1, T102.1 (C)
unnamed: R402.2, T103.2 (B)
unnamed: R403.1, R404.1, R405.1, T103.1 (C)
unnamed: R406.2, T104.2 (B)
unnamed: R407.1, R408.1, R409.1, T104.1 (C)
unnamed: IC14.9 (QH*), IC15.14 (SER)
unnamed: R410.2, T105.2 (B)
unnamed: R411.1, R412.1, R413.1, T105.1 (C)
unnamed: R414.2, T106.2 (B)
unnamed: R415.1, R416.1, R417.1, T106.1 (C)
unnamed: R418.2, T107.2 (B)
unnamed: R419.1, R420.1, R421.1, T107.1 (C)
unnamed: R422.2, T108.2 (B)
unnamed: R423.1, R424.1, R425.1, T108.1 (C)
unnamed: R426.2, T109.2 (B)
unnamed: R427.1, R428.1, R429.1, T109.1 (C)
unnamed: R430.2, T110.2 (B)
unnamed: R431.1, R432.1, R433.1, T110.1 (C)
unnamed: R434.2, T111.2 (B)
unnamed: R435.1, R436.1, R437.1, T111.1 (C)
unnamed: R438.2, T112.2 (B)
unnamed: R439.1, R440.1, R441.1, T112.1 (C)
unnamed: IC15.9 (QH*), IC16.14 (SER)
unnamed: R442.2, T113.2 (B)
unnamed: R443.1, R444.1, R445.1, T113.1 (C)
unnamed: R446.2, T114.2 (B)
unnamed: R447.1, R448.1, R449.1, T114.1 (C)
unnamed: R450.2, T115.2 (B)
unnamed: R451.1, R452.1, R453.1, T115.1 (C)
unnamed: R454.2, T116.2 (B)
unnamed: R455.1, R456.1, R457.1, T116.1 (C)
unnamed: R458.2, T117.2 (B)
unnamed: R459.1, R460.1, R461.1, T117.1 (C)
unnamed: R462.2, T118.2 (B)
unnamed: R463.1, R464.1, R465.1, T118.1 (C)
unnamed: R466.2, T119.2 (B)
unnamed: R467.1, R468.1, R469.1, T119.1 (C)
unnamed: R470.2, T120.2 (B)
unnamed: R471.1, R472.1, R473.1, T120.1 (C)
unnamed: IC16.9 (QH*), IC17.14 (SER)
unnamed: R474.2, T121.2 (B)
unnamed: R475.1, R476.1, R477.1, T121.1 (C)
unnamed: R478.2, T122.2 (B)
unnamed: R479.1, R480.1, R481.1, T122.1 (C)
unnamed: R482.2, T123.2 (B)
unnamed: R483.1, R484.1, R485.1, T123.1 (C)
unnamed: R486.2, T124.2 (B)
unnamed: R487.1, R488.1, R489.1, T124.1 (C)
unnamed: R490.2, T125.2 (B)
unnamed: R491.1, R492.1, R493.1, T125.1 (C)
unnamed: R494.2, T126.2 (B)
unnamed: R495.1, R496.1, R497.1, T126.1 (C)
unnamed: R498.2, T127.2 (B)
unnamed: R499.1, R500.1, R501.1, T127.1 (C)
unnamed: R502.2, T128.2 (B)
unnamed: R503.1, R504.1, R505.1, T128.1 (C)
unnamed: IC17.9 (QH*), IC18.14 (SER)
unnamed: R506.2, T129.2 (B)
unnamed: R507.1, R508.1, R509.1, T129.1 (C)
unnamed: R510.2, T130.2 (B)
unnamed: R511.1, R512.1, R513.1, T130.1 (C)
unnamed: R514.2, T131.2 (B)
unnamed: R515.1, R516.1, R517.1, T131.1 (C)
unnamed: R518.2, T132.2 (B)
unnamed: R519.1, R520.1, R521.1, T132.1 (C)
unnamed: R522.2, T133.2 (B)
unnamed: R523.1, R524.1, R525.1, T133.1 (C)
unnamed: R526.2, T134.2 (B)
unnamed: R527.1, R528.1, R529.1, T134.1 (C)
unnamed: R530.2, T135.2 (B)
unnamed: R531.1, R532.1, R533.1, T135.1 (C)
unnamed: R534.2, T136.2 (B)
unnamed: R535.1, R536.1, R537.1, T136.1 (C)
unnamed: IC18.9 (QH*), IC19.14 (SER)
unnamed: R538.2, T137.2 (B)
unnamed: R539.1, R540.1, T137.1 (C)
unnamed: R542.2, T138.2 (B)
unnamed: R543.1, R544.1, T138.1 (C)
unnamed: R546.2, T139.2 (B)
unnamed: R547.1, R548.1, T139.1 (C)
unnamed: R550.2, T140.2 (B)
unnamed: R551.1, R552.1, T140.1 (C)
unnamed: R554.2, T141.2 (B)
unnamed: R555.1, R556.1, T141.1 (C)
unnamed: R558.2, T142.2 (B)
unnamed: R559.1, R560.1, T142.1 (C)
unnamed: R562.2, T143.2 (B)
unnamed: R563.1, R564.1, T143.1 (C)
unnamed: R566.2, T144.2 (B)
unnamed: R567.1, R568.1, T144.1 (C)
unnamed: IC19.9 (QH*), IC20.14 (SER)
unnamed: R541.2, T145.2 (B)
unnamed: R545.1, R549.1, T145.1 (C)
unnamed: R553.2, T146.2 (B)
unnamed: R557.1, R561.1, T146.1 (C)
unnamed: R565.2, T147.2 (B)
unnamed: R569.1, R570.1, T147.1 (C)
unnamed: R571.2, T148.2 (B)
unnamed: R572.1, R573.1, T148.1 (C)
unnamed: R574.2, T149.2 (B)
unnamed: R575.1, R576.1, T149.1 (C)
unnamed: R577.2, T150.2 (B)
unnamed: R578.1, R579.1, T150.1 (C)
unnamed: R580.2, T151.2 (B)
unnamed: R581.1, R582.1, T151.1 (C)
unnamed: R583.2, T152.2 (B)
unnamed: R584.1, R585.1, T152.1 (C)
unnamed: IC20.9 (QH*), IC21.14 (SER)
unnamed: R586.2, T153.2 (B)
unnamed: R587.1, R588.1, T153.1 (C)
unnamed: R589.2, T154.2 (B)
unnamed: R590.1, R591.1, T154.1 (C)
unnamed: R592.2, T155.2 (B)
unnamed: R593.1, R594.1, T155.1 (C)
unnamed: R595.2, T156.2 (B)
unnamed: R596.1, R597.1, T156.1 (C)
unnamed: R598.2, T157.2 (B)
unnamed: R599.1, R600.1, T157.1 (C)
unnamed: R601.2, T158.2 (B)
unnamed: R602.1, R603.1, T158.1 (C)
unnamed: R604.2, T159.2 (B)
unnamed: R605.1, R606.1, T159.1 (C)
unnamed: R607.2, T160.2 (B)
unnamed: R608.1, R609.1, T160.1 (C)
unnamed: IC21.9 (QH*), IC22.14 (SER)
unnamed: R610.2, T161.2 (B)
unnamed: R611.1, R612.1, T161.1 (C)
unnamed: R613.2, T162.2 (B)
unnamed: R614.1, R615.1, T162.1 (C)
unnamed: R616.2, T163.2 (B)
unnamed: R617.1, R618.1, T163.1 (C)
unnamed: R619.2, T164.2 (B)
unnamed: R620.1, R621.1, T164.1 (C)
unnamed: R622.2, T165.2 (B)
unnamed: R623.1, R624.1, T165.1 (C)
unnamed: R625.2, T166.2 (B)
unnamed: R626.1, R627.1, T166.1 (C)
unnamed: R628.2, T167.2 (B)
unnamed: R629.1, R630.1, T167.1 (C)
unnamed: R631.2, T168.2 (B)
unnamed: R632.1, R633.1, T168.1 (C)
unnamed: IC22.9 (QH*), IC23.14 (SER)
unnamed: R634.2, T169.2 (B)
unnamed: R635.1, R636.1, T169.1 (C)
unnamed: R637.2, T170.2 (B)
unnamed: R638.1, R639.1, T170.1 (C)
unnamed: R640.2, T171.2 (B)
unnamed: R641.1, R642.1, T171.1 (C)
unnamed: R643.2, T172.2 (B)
unnamed: R644.1, R645.1, T172.1 (C)
unnamed: R646.2, T173.2 (B)
unnamed: R647.1, R648.1, T173.1 (C)
unnamed: R649.2, T174.2 (B)
unnamed: R650.1, R651.1, T174.1 (C)
unnamed: R652.2, T175.2 (B)
unnamed: R653.1, R654.1, T175.1 (C)
unnamed: R655.2, T176.2 (B)
unnamed: R656.1, R657.1, T176.1 (C)
unnamed: IC23.9 (QH*), IC24.14 (SER)
unnamed: R658.2, T177.2 (B)
unnamed: R659.1, R660.1, T177.1 (C)
unnamed: R661.2, T178.2 (B)
unnamed: R662.1, R663.1, T178.1 (C)
unnamed: R664.2, T179.2 (B)
unnamed: R665.1, R666.1, T179.1 (C)
unnamed: R667.2, T180.2 (B)
unnamed: R668.1, R669.1, T180.1 (C)
unnamed: R670.2, T181.2 (B)
unnamed: R671.1, R672.1, T181.1 (C)
unnamed: R673.2, T182.2 (B)
unnamed: R674.1, R675.1, T182.1 (C)
unnamed: R676.2, T183.2 (B)
unnamed: R677.1, R678.1, T183.1 (C)
unnamed: R679.2, T184.2 (B)
unnamed: R680.1, R681.1, T184.1 (C)
unnamed: IC24.9 (QH*), IC25.14 (SER)
unnamed: R682.2, T185.2 (B)
unnamed: R683.1, R684.1, T185.1 (C)
unnamed: R685.2, T186.2 (B)
unnamed: R686.1, R687.1, T186.1 (C)
unnamed: R688.2, T187.2 (B)
unnamed: R689.1, R690.1, T187.1 (C)
unnamed: R691.2, T188.2 (B)
unnamed: R692.1, R693.1, T188.1 (C)
unnamed: R694.2, T189.2 (B)
unnamed: R695.1, R696.1, T189.1 (C)
unnamed: R697.2, T190.2 (B)
unnamed: R698.1, R699.1, T190.1 (C)
unnamed: R700.2, T191.2 (B)
unnamed: R701.1, R702.1, T191.1 (C)
unnamed: R703.2, T192.2 (B)
unnamed: R704.1, R705.1, T192.1 (C)
unnamed: IC25.9 (QH*), IC26.14 (SER)
unnamed: R706.2, T193.2 (B)
unnamed: R707.1, R708.1, T193.1 (C)
unnamed: R709.2, T194.2 (B)
unnamed: R710.1, R711.1, T194.1 (C)
unnamed: R712.2, T195.2 (B)
unnamed: R713.1, R714.1, T195.1 (C)
unnamed: R715.2, T196.2 (B)
unnamed: R716.1, R717.1, T196.1 (C)
unnamed: R718.2, T197.2 (B)
unnamed: R719.1, R720.1, T197.1 (C)
unnamed: R721.2, T198.2 (B)
unnamed: R722.1, R723.1, T198.1 (C)
unnamed: R724.2, T199.2 (B)
unnamed: R725.1, R726.1, T199.1 (C)
unnamed: R727.2, T200.2 (B)
unnamed: R728.1, R729.1, T200.1 (C)
unnamed: C39.1, SV2.5
RE_IN_0: IC20.15 (QA), R541.1
RE_IN_1: IC20.1 (QB), R553.1
RE_IN_2: IC20.2 (QC), R565.1
RE_IN_3: IC20.3 (QD), R571.1
RE_IN_4: IC20.4 (QE), R574.1
RE_IN_5: IC20.5 (QF), R577.1
RE_IN_6: IC20.6 (QG), R580.1
RE_IN_7: IC20.7 (QH), R583.1
RE_IN_8: IC21.15 (QA), R586.1
RE_IN_9: IC21.1 (QB), R589.1
RE_IN_10: IC21.2 (QC), R592.1
RE_IN_11: IC21.3 (QD), R595.1
RE_IN_12: IC21.4 (QE), R598.1
RE_IN_13: IC21.5 (QF), R601.1
RE_IN_14: IC21.6 (QG), R604.1
RE_IN_15: IC21.7 (QH), R607.1
RE_IN_16: IC22.15 (QA), R610.1
RE_IN_17: IC22.1 (QB), R613.1
RE_IN_18: IC22.2 (QC), R616.1
RE_IN_19: IC22.3 (QD), R619.1
RE_IN_20: IC22.4 (QE), R622.1
RE_IN_21: IC22.5 (QF), R625.1
RE_IN_22: IC22.6 (QG), R628.1
RE_IN_23: IC22.7 (QH), R631.1
RE_IN_24: IC23.15 (QA), R634.1
RE_IN_25: IC23.1 (QB), R637.1
RE_IN_26: IC23.2 (QC), R640.1
RE_IN_27: IC23.3 (QD), R643.1
RE_IN_28: IC23.4 (QE), R646.1
RE_IN_29: IC23.5 (QF), R649.1
RE_IN_30: IC23.6 (QG), R652.1
RE_IN_31: IC23.7 (QH), R655.1
RE_IN_32: IC24.15 (QA), R658.1
RE_IN_33: IC24.1 (QB), R661.1
RE_IN_34: IC24.2 (QC), R664.1
RE_IN_35: IC24.3 (QD), R667.1
RE_IN_36: IC24.4 (QE), R670.1
RE_IN_37: IC24.5 (QF), R673.1
RE_IN_38: IC24.6 (QG), R676.1
RE_IN_39: IC24.7 (QH), R679.1
RE_IN_40: IC25.15 (QA), R682.1
RE_IN_41: IC25.1 (QB), R685.1
RE_IN_42: IC25.2 (QC), R688.1
RE_IN_43: IC25.3 (QD), R691.1
RE_IN_44: IC25.4 (QE), R694.1
RE_IN_45: IC25.5 (QF), R697.1
RE_IN_46: IC25.6 (QG), R700.1
RE_IN_47: IC25.7 (QH), R703.1
RE_IN_48: IC26.15 (QA), R706.1
RE_IN_49: IC26.1 (QB), R709.1
RE_IN_50: IC26.2 (QC), R712.1
RE_IN_51: IC26.3 (QD), R715.1
RE_IN_52: IC26.4 (QE), R718.1
RE_IN_53: IC26.5 (QF), R721.1
RE_IN_54: IC26.6 (QG), R724.1
RE_IN_55: IC26.7 (QH), R727.1
RE_IN_56: IC11.15 (QA), R538.1
RE_IN_57: IC11.1 (QB), R542.1
RE_IN_58: IC11.2 (QC), R546.1
RE_IN_59: IC11.3 (QD), R550.1
RE_IN_60: IC11.4 (QE), R554.1
RE_IN_61: IC11.5 (QF), R558.1
RE_IN_62: IC11.6 (QG), R562.1
RE_IN_63: IC11.7 (QH), R566.1
RE_OU_0: R549.2
RE_OU_1: R561.2
RE_OU_2: R570.2
RE_OU_3: R573.2
RE_OU_4: R576.2
RE_OU_5: R579.2
RE_OU_6: R582.2
RE_OU_7: R585.2
RE_OU_8: R588.2
RE_OU_9: R591.2
RE_OU_10: R594.2
RE_OU_11: R597.2
RE_OU_12: R600.2
RE_OU_13: R603.2
RE_OU_14: R606.2
RE_OU_15: R609.2
RE_OU_16: R612.2
RE_OU_17: R615.2
RE_OU_18: R618.2
RE_OU_19: R621.2
RE_OU_20: R624.2
RE_OU_21: R627.2
RE_OU_22: R630.2
RE_OU_23: R633.2
RE_OU_24: R636.2
RE_OU_25: R639.2
RE_OU_26: R642.2
RE_OU_27: R645.2
RE_OU_28: R648.2
RE_OU_29: R651.2
RE_OU_30: R654.2
RE_OU_31: R657.2
RE_OU_32: R660.2
RE_OU_33: R663.2
RE_OU_34: R666.2
RE_OU_35: R669.2
RE_OU_36: R672.2
RE_OU_37: R675.2
RE_OU_38: R678.2
RE_OU_39: R681.2
RE_OU_40: R684.2
RE_OU_41: R687.2
RE_OU_42: R690.2
RE_OU_43: R693.2
RE_OU_44: R696.2
RE_OU_45: R699.2
RE_OU_46: R702.2
RE_OU_47: R705.2
RE_OU_48: R708.2
RE_OU_49: R711.2
RE_OU_50: R714.2
RE_OU_51: R717.2
RE_OU_52: R720.2
RE_OU_53: R723.2
RE_OU_54: R726.2
RE_OU_55: R729.2
RE_OU_56: R540.2
RE_OU_57: R544.2
RE_OU_58: R548.2
RE_OU_59: R552.2
RE_OU_60: R556.2
RE_OU_61: R560.2
RE_OU_62: R564.2
RE_OU_63: R568.2
RX_TO_MICRO: IC2.2 ((RXD)PD0), SV1.3
TX_FROM_MICRO: IC2.3 ((TXD)PD1), SV1.4

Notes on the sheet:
Keep Close to Micro's Power Pins

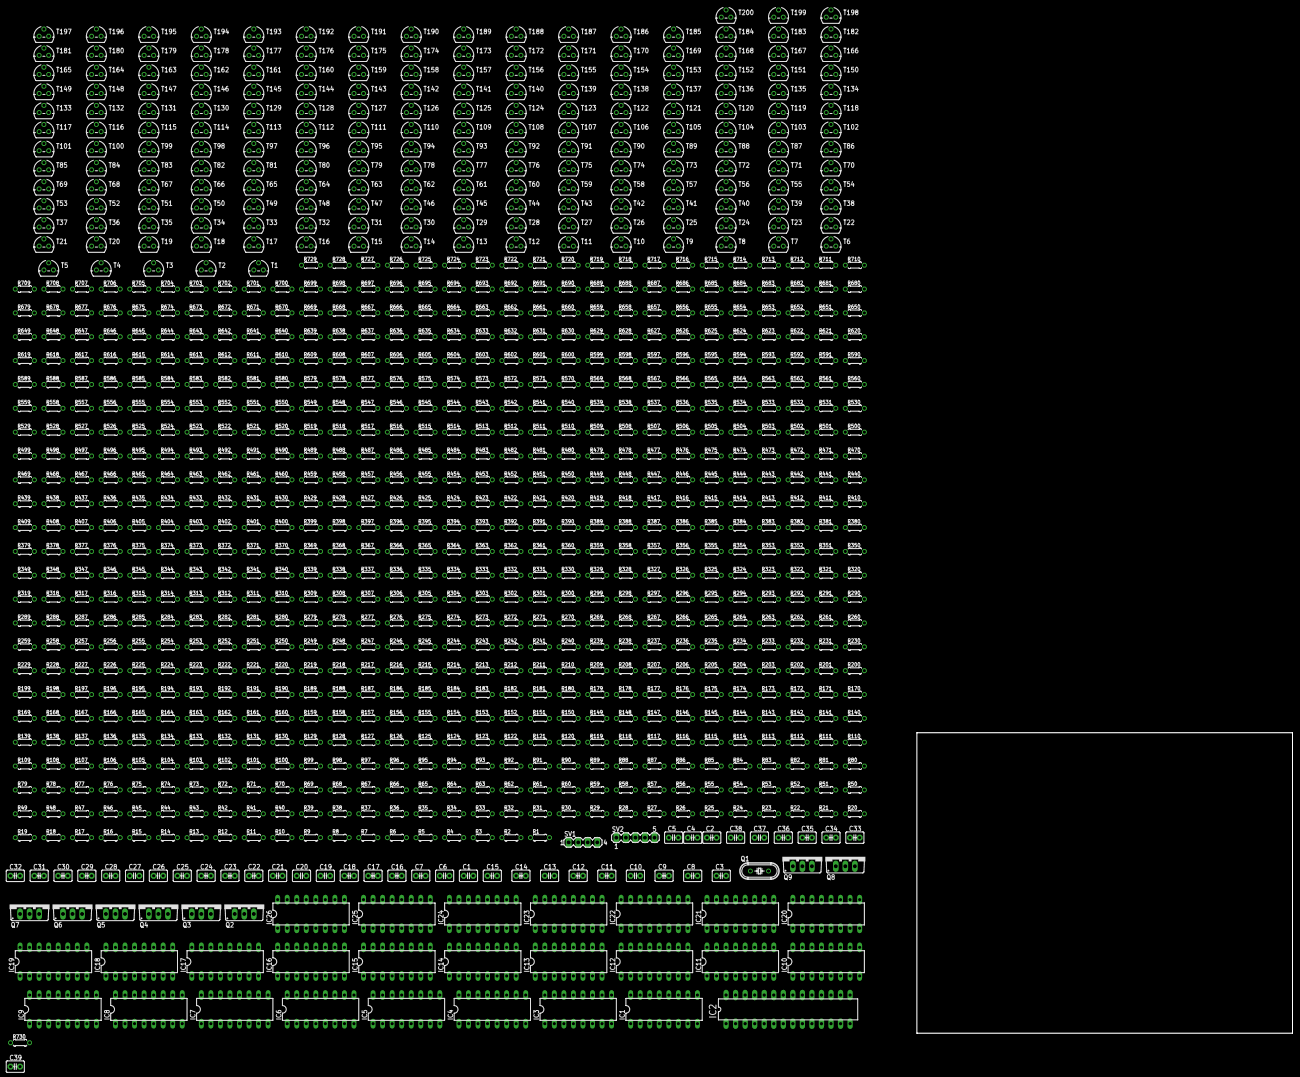
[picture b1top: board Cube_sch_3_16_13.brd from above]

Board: 2 copper layers, 100.0 x 80.0 mm, 1006 parts (0 on the bottom side), 763 nets, no tracks yet.

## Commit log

2017-12-14 Updating original files
2017-12-14 Updating original files- Eagle
2017-12-14 Updating original files- added missing pinout helper
2017-12-14 Basic code added
2017-12-20 byte-arra implpimented
2017-12-20 updated logs
2017-12-20 video added (initial test)
2017-12-21 Doc added
